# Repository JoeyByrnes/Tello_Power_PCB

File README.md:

# Tello Power PCB
Hardware Design Files for Tello Power Regulation/Distribution PCB

## Main Power PCB
<hr>
<br>

<br>

## XT30 Expansion PCB
<hr>
<br>

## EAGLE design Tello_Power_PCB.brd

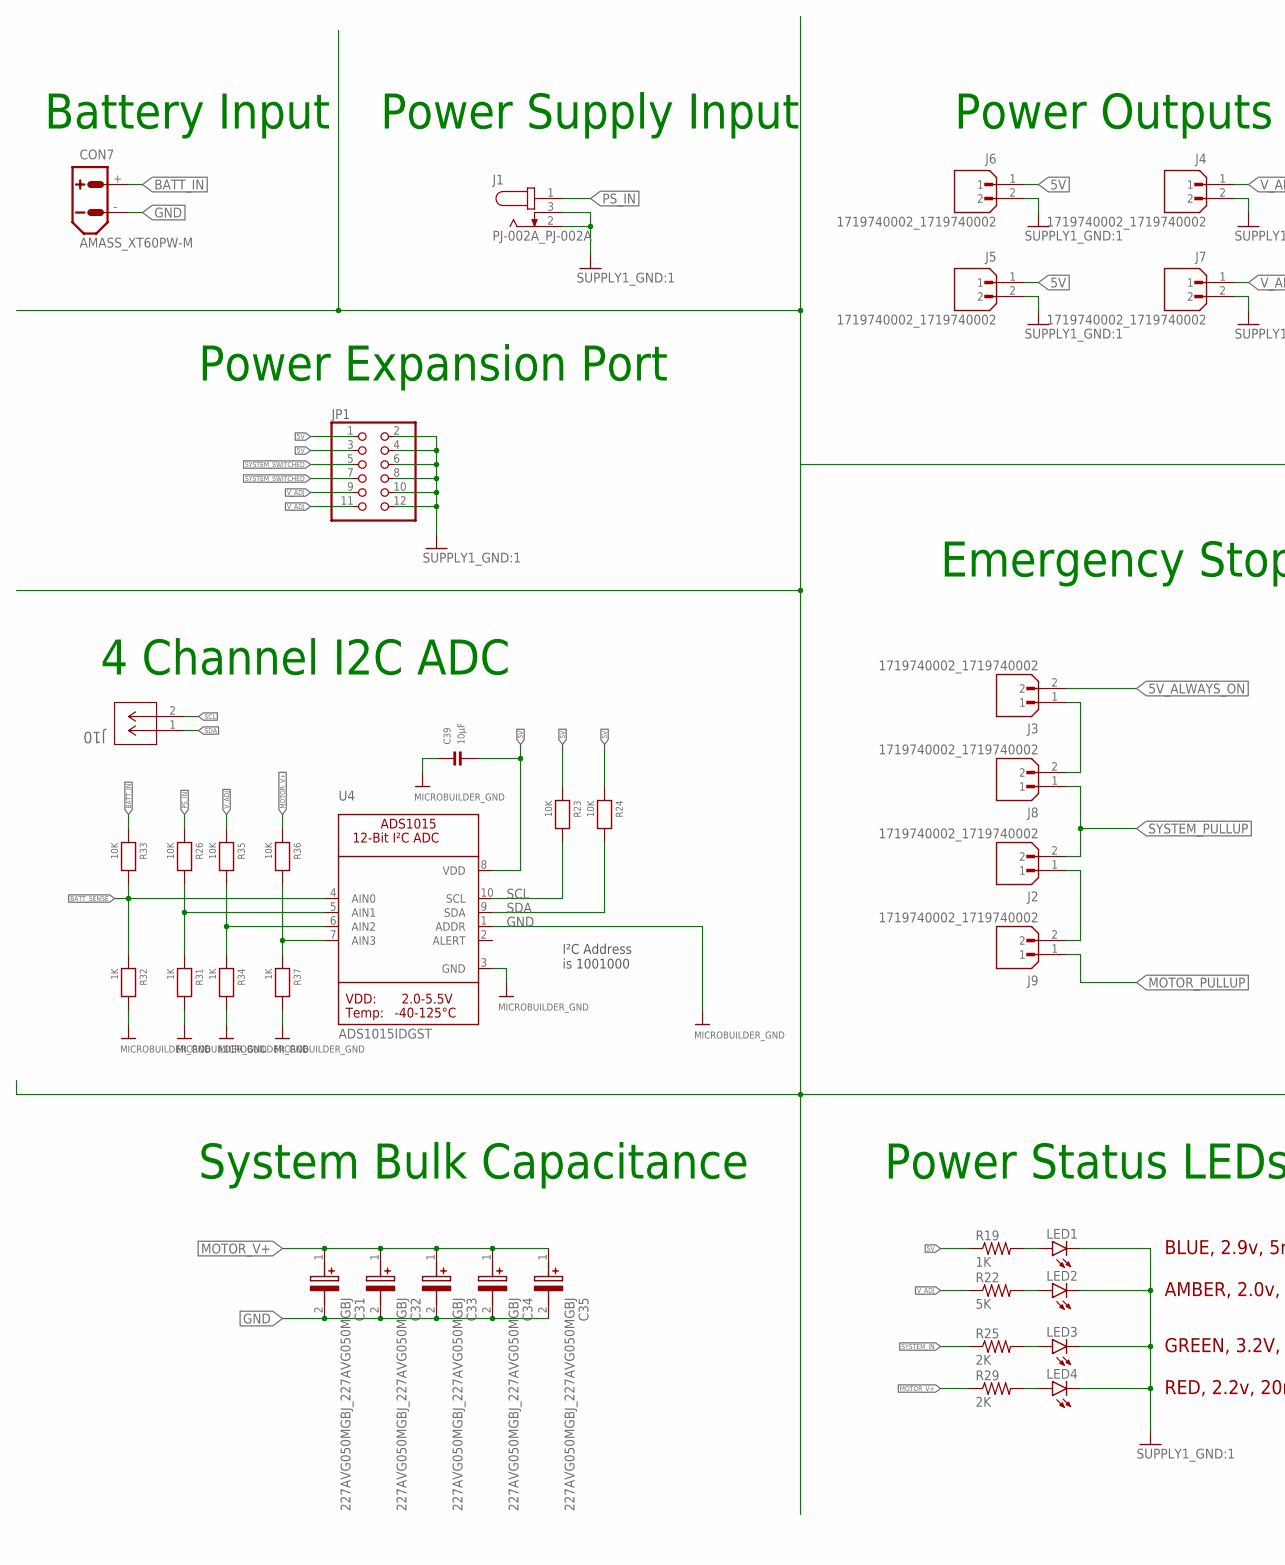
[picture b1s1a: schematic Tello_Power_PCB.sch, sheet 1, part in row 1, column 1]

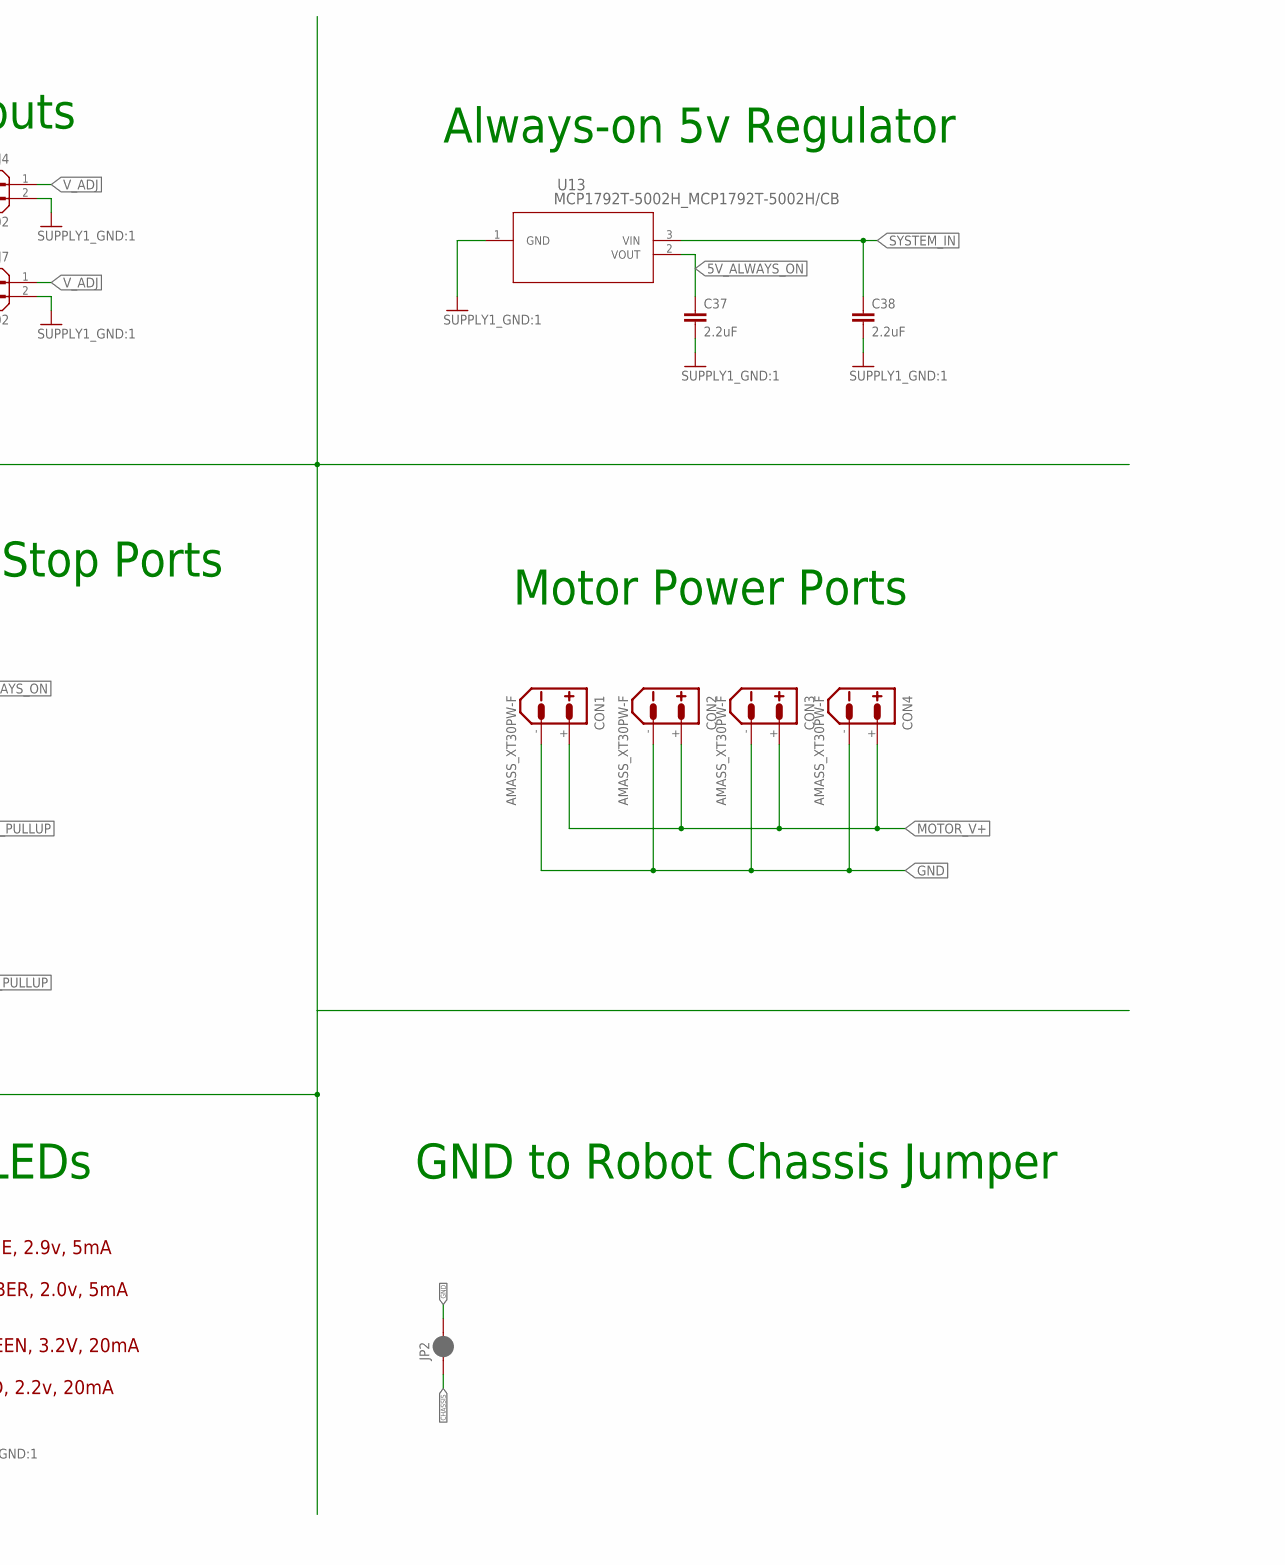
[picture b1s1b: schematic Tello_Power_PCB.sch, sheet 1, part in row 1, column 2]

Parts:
C31, C32, C33, C34, C35: 227AVG050MGBJ_227AVG050MGBJ; 227AVG050MGBJ_CAPPRD500W60D1025H1350
C37: 2.2uF; RCL_C0603
C38: 2.2uF; RCL_C1206
C39: 10µF; MICROBUILDER_0603:1
CON1, CON2, CON3, CON4: AMASS_XT30PW-F
CON7: AMASS_XT60PW-M
J1: PJ-002A_PJ-002A; PJ-002A_CUI_PJ-002A
J2, J3, J4, J5, J6, J7, J8, J9: 1719740002_1719740002; 1719740002_MOLEX_1719740002
J10: SM02B-GHS-TB_SM02BGHSTBLFSN; SM02B-GHS-TB_CONN_SM02BGHSTB_JST
JP1: PINHEAD_PINHD-2X6; PINHEAD_2X06
JP2: SPARKFUN-JUMPERS_JUMPER-SMT_2_NC_PASTE_NO-SILK; SPARKFUN-JUMPERS_SMT-JUMPER_2_NC_PASTE_NO-SILK
LED1, LED2, LED3, LED4: LED_LEDCHIP-LED0603; LED_CHIP-LED0603
R19: 1K; RCL_R0603
R22: 5K; RCL_R0603
R23, R24, R26, R33, R35, R36: 10K; MICROBUILDER_0603:1
R25, R29: 2K; RCL_R0603
R31, R32, R34, R37: 1K; MICROBUILDER_0603:1
U4: ADS1015IDGST; MICROBUILDER_MSOP10
U13: MCP1792T-5002H_MCP1792T-5002H/CB; MCP1792T-5002H_SOT-23A_CB_MCH

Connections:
5V: C39.2, J5.1, J6.1, JP1.1, JP1.3, R19.1, R23.1, R24.1, U4.8 (VDD); also elsewhere on the board
5V_ALWAYS_ON: C37.1, J3.2, U13.2 (VOUT); also elsewhere on the board
BATT_IN: CON7.+, R33.1; also elsewhere on the board
BATT_SENSE: R32.1, R33.2, U4.4 (AIN0)
CHASSIS: JP2.1
GND: C31.2 (-), C32.2 (-), C33.2 (-), C34.2 (-), C35.2 (-), C37.2, C38.2, C39.1, CON1.-, CON2.-, CON3.-, CON4.-, CON7.-, J1.2, J1.3, J4.2, J5.2, J6.2, J7.2, JP1.2, JP1.4, JP1.6, JP1.8, JP1.10, JP1.12, JP2.2, LED1.C, LED2.C, LED3.C, LED4.C, R31.2, R32.2, R34.2, R37.2, U4.1 (ADDR), U4.3 (GND), U13.1 (GND); also elsewhere on the board
MOTOR_PULLUP: J9.1; also elsewhere on the board
MOTOR_V+: C31.1 (+), C32.1 (+), C33.1 (+), C34.1 (+), C35.1 (+), CON1.+, CON2.+, CON3.+, CON4.+, R29.1, R36.1; also elsewhere on the board
unnamed: LED4.A, R29.2
unnamed: R26.2, R31.1, U4.5 (AIN1)
unnamed: J2.1, J9.2
unnamed: R34.1, R35.2, U4.6 (AIN2)
unnamed: J3.1, J8.2
unnamed: R36.2, R37.1, U4.7 (AIN3)
unnamed: LED3.A, R25.2
unnamed: LED2.A, R22.2
unnamed: LED1.A, R19.2
PS_IN: J1.1, R26.1; also elsewhere on the board
SCL: J10.2, R23.2, U4.10 (SCL)
SDA: J10.1, R24.2, U4.9 (SDA)
SYSTEM_IN: C38.1, R25.1, U13.3 (VIN); also elsewhere on the board
SYSTEM_PULLUP: J2.2, J8.1; also elsewhere on the board
SYSTEM_SWITCHED: JP1.5, JP1.7; also elsewhere on the board
V_ADJ: J4.1, J7.1, JP1.9, JP1.11, R22.1, R35.1; also elsewhere on the board

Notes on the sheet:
Power Supply Input
Battery Input
RED, 2.2v, 20mA
GREEN, 3.2V, 20mA
AMBER, 2.0v, 5mA
BLUE, 2.9v, 5mA
Power Outputs
Power Expansion Port
System Bulk Capacitance
Power Status LEDs
Emergency Stop Ports
Motor Power Ports
Always-on 5v Regulator
GND to Robot Chassis Jumper
I²C Address is 1001000
4 Channel I2C ADC

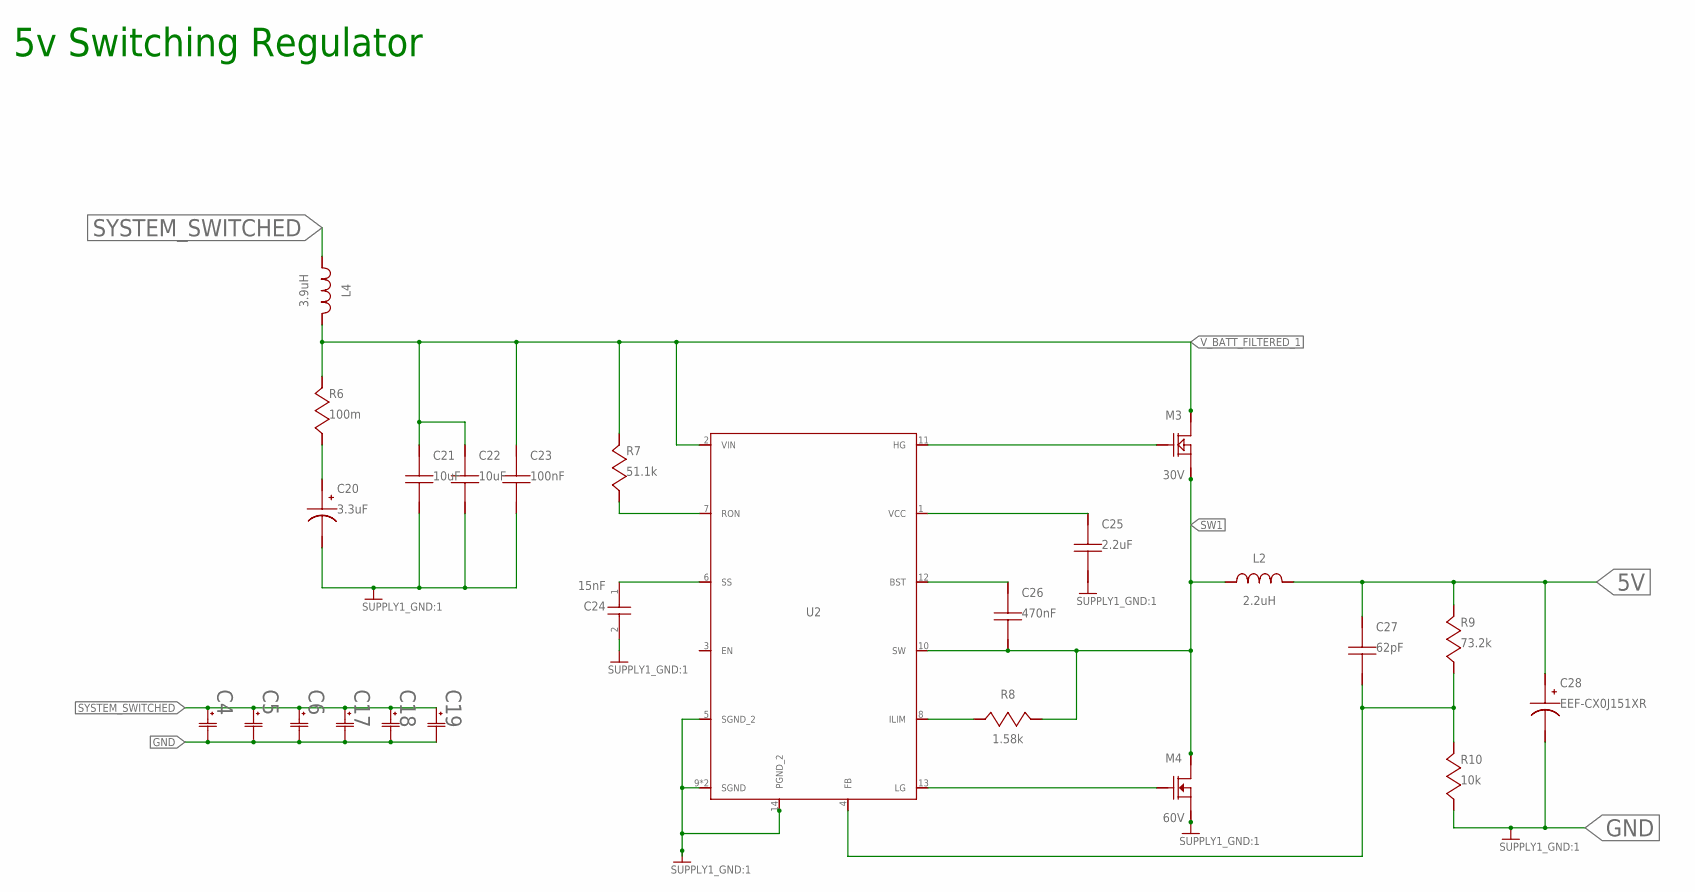
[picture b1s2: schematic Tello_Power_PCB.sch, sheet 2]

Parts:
C4, C5, C6, C17, C18, C19: PCR1H820MCL1GS_PCR1H820MCL1GS; PCR1H820MCL1GS_CAP_PC_10X8_NCH
C20: 3.3uF; 5V-LM3150MH_6032-28
C21, C22: 10uF; 5V-LM3150MH_0805
C23: 100nF; 5V-LM3150MH_0603
C24: 15nF; CGA4F2C0G1H153J085AA_CAPC2012X100N
C25: 2.2uF; 5V-LM3150MH_0805
C26: 470nF; 5V-LM3150MH_1206
C27: 62pF; 5V-LM3150MH_0805
C28: EEF-CX0J151XR; 5V-LM3150MH_C2917
L2: 2.2uH; 5V-LM3150MH_XAL5030
L4: 3.9uH; 5V-LM3150MH_IND_NPI43C
M3: 30V; 5V-LM3150MH_TRANS_NEXFET_Q5A
M4: 60V; 5V-LM3150MH_TRANS_NEXFET_Q5A
R6: 100m; 5V-LM3150MH_0603
R7: 51.1k; 5V-LM3150MH_0805
R8: 1.58k; 5V-LM3150MH_0805
R9: 73.2k; 5V-LM3150MH_0805
R10: 10k; 5V-LM3150MH_0805
U2: 5V-LM3150MH_LM3150MH/NOPB; 5V-LM3150MH_MXA14A

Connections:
5V: C27.1, C28.P$1 (+), L2.2, R9.1; also elsewhere on the board
GND: C4.2, C5.2, C6.2, C17.2, C18.2, C19.2, C20.2 (-), C21.2, C22.2, C23.2, C24.2, C25.2, C28.P$2 (-), M4.1 (SOURCE), M4.2 (SOURCE), M4.3 (SOURCE), R10.2, U2.5 (SGND_2), U2.9 (SGND), U2.14 (PGND_2), U2.15 (SGND); also elsewhere on the board
unnamed: R7.2, U2.7 (RON)
unnamed: C24.1, U2.6 (SS)
unnamed: C20.1 (+), R6.2
unnamed: R8.2, U2.8 (ILIM)
unnamed: C26.1, U2.12 (BST)
unnamed: C25.1, U2.1 (VCC)
unnamed: M3.4 (GATE), U2.11 (HG)
unnamed: M4.4 (GATE), U2.13 (LG)
unnamed: C27.2, R9.2, R10.1, U2.4 (FB)
SW1: C26.2, L2.1, M3.1 (SOURCE), M3.2 (SOURCE), M3.3 (SOURCE), M4.5 (DRAIN), M4.6 (DRAIN), M4.7 (DRAIN), M4.8 (DRAIN), M4.9 (DRAIN), R8.1, U2.10 (SW)
SYSTEM_SWITCHED: C4.1, C5.1, C6.1, C17.1, C18.1, C19.1, L4.1; also elsewhere on the board
V_BATT_FILTERED_1: C21.1, C22.1, C23.1, L4.2, M3.5 (DRAIN), M3.6 (DRAIN), M3.7 (DRAIN), M3.8 (DRAIN), M3.9 (DRAIN), R6.1, R7.1, U2.2 (VIN)

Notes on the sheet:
5v Switching Regulator

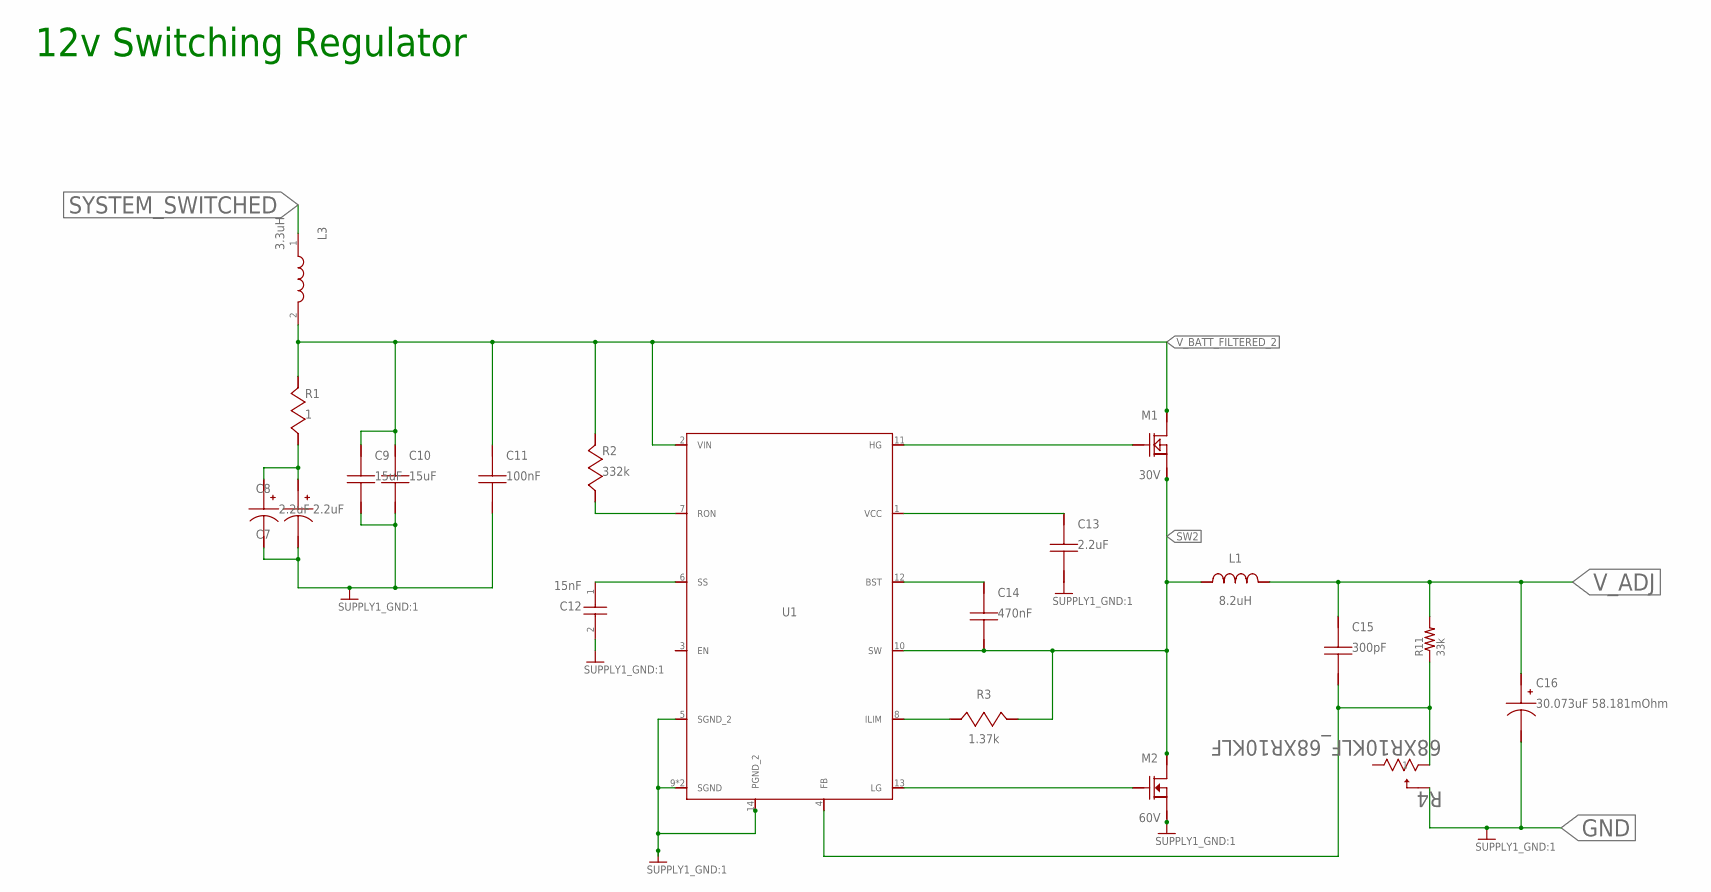
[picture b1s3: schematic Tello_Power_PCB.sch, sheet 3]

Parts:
C7, C8: 2.2uF; 12V--LM3150_3528-21
C9, C10: 15uF; 12V--LM3150_0805:1
C11: 100nF; 12V--LM3150_0402
C12: 15nF; CGA4F2C0G1H153J085AA_CAPC2012X100N
C13: 2.2uF; 12V--LM3150_0805:1
C14: 470nF; 12V--LM3150_1206:1
C15: 300pF; 12V--LM3150_0805:1
C16: 30.073uF 58.181mOhm; 12V--LM3150_PCV1E330MCL1GS
L1: 8.2uH; 12V--LM3150_WE-LHMI_8040
L3: 3.3uH; XAL4030-332MEB_XAL4030-332MEB
M1: 30V; 12V--LM3150_TRANS_NEXFET_Q5A:1
M2: 60V; 12V--LM3150_TRANS_NEXFET_Q5A:1
R1: 1; 12V--LM3150_0402
R2: 332k; 12V--LM3150_0805:1
R3: 1.37k; 12V--LM3150_0805:1
R4: 68XR10KLF_68XR10KLF; 68XR10KLF_RES3_68X_TTE
R11: 33k; RCL_R0805
U1: 5V-LM3150MH_LM3150MH/NOPB; 5V-LM3150MH_MXA14A

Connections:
GND: C7.2 (-), C8.2 (-), C9.2, C10.2, C11.2, C12.2, C13.2, C16.P$3 (-), M2.1 (SOURCE), M2.2 (SOURCE), M2.3 (SOURCE), R4.2, U1.5 (SGND_2), U1.9 (SGND), U1.14 (PGND_2), U1.15 (SGND); also elsewhere on the board
unnamed: C7.1 (+), C8.1 (+), R1.2
unnamed: R2.2, U1.7 (RON)
unnamed: C12.1, U1.6 (SS)
unnamed: R3.2, U1.8 (ILIM)
unnamed: C14.1, U1.12 (BST)
unnamed: C13.1, U1.1 (VCC)
unnamed: M1.4 (GATE), U1.11 (HG)
unnamed: M2.4 (GATE), U1.13 (LG)
unnamed: C15.2, R4.3 (1), R11.1, U1.4 (FB)
SW2: C14.2, L1.1, M1.1 (SOURCE), M1.2 (SOURCE), M1.3 (SOURCE), M2.5 (DRAIN), M2.6 (DRAIN), M2.7 (DRAIN), M2.8 (DRAIN), M2.9 (DRAIN), R3.1, U1.10 (SW)
SYSTEM_SWITCHED: L3.1; also elsewhere on the board
V_ADJ: C15.1, C16.P$1 (+), L1.2, R11.2; also elsewhere on the board
V_BATT_FILTERED_2: C9.1, C10.1, C11.1, L3.2, M1.5 (DRAIN), M1.6 (DRAIN), M1.7 (DRAIN), M1.8 (DRAIN), M1.9 (DRAIN), R1.1, R2.1, U1.2 (VIN)

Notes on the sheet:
12v Switching Regulator

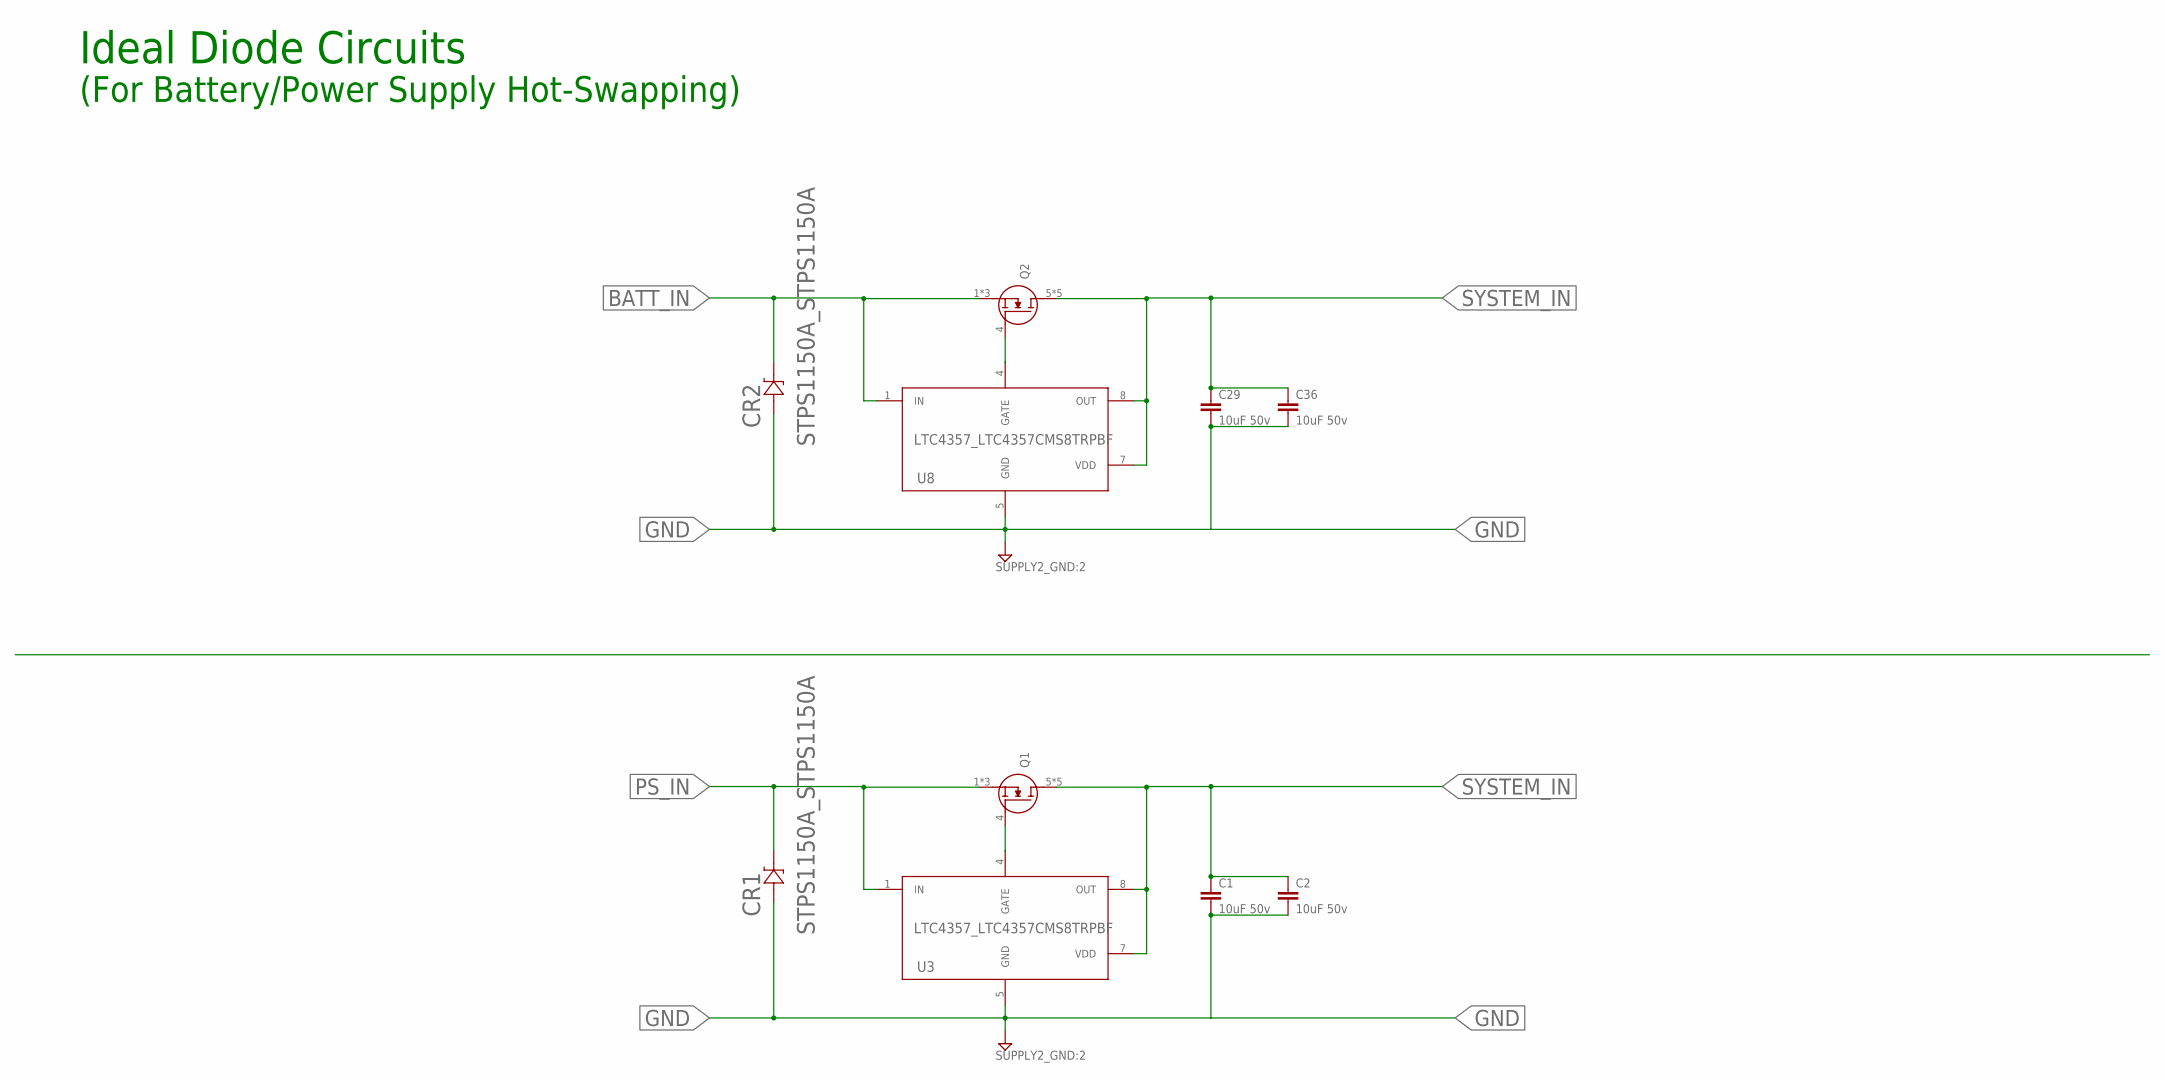
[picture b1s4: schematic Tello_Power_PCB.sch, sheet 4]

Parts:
C1, C2, C29, C36: 10uF 50v; RCL_C1206
CR1, CR2: STPS1150A_STPS1150A; STPS1150A_SMA_STM
Q1, Q2: BSC027N06LS5ATMA1_BSC027N06LS5ATMA1
U3, U8: LTC4357_LTC4357CMS8TRPBF; LTC4357_MSOP-8_MS_LIT

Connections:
BATT_IN: CR2.1, Q2.1 (S), Q2.2 (S), Q2.3 (S), U8.1 (IN); also elsewhere on the board
GND: C1.2, C2.2, C29.2, C36.2, CR1.2, CR2.2, U3.5 (GND), U8.5 (GND); also elsewhere on the board
unnamed: Q1.4 (G), U3.4 (GATE)
unnamed: Q2.4 (G), U8.4 (GATE)
PS_IN: CR1.1, Q1.1 (S), Q1.2 (S), Q1.3 (S), U3.1 (IN); also elsewhere on the board
SYSTEM_IN: C1.1, C2.1, C29.1, C36.1, Q1.5 (D), Q1.6 (D), Q1.7 (D), Q1.8 (D), Q1.9 (D), Q2.5 (D), Q2.6 (D), Q2.7 (D), Q2.8 (D), Q2.9 (D), U3.7 (VDD), U3.8 (OUT), U8.7 (VDD), U8.8 (OUT); also elsewhere on the board

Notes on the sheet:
Ideal Diode Circuits
(For Battery/Power Supply Hot-Swapping)

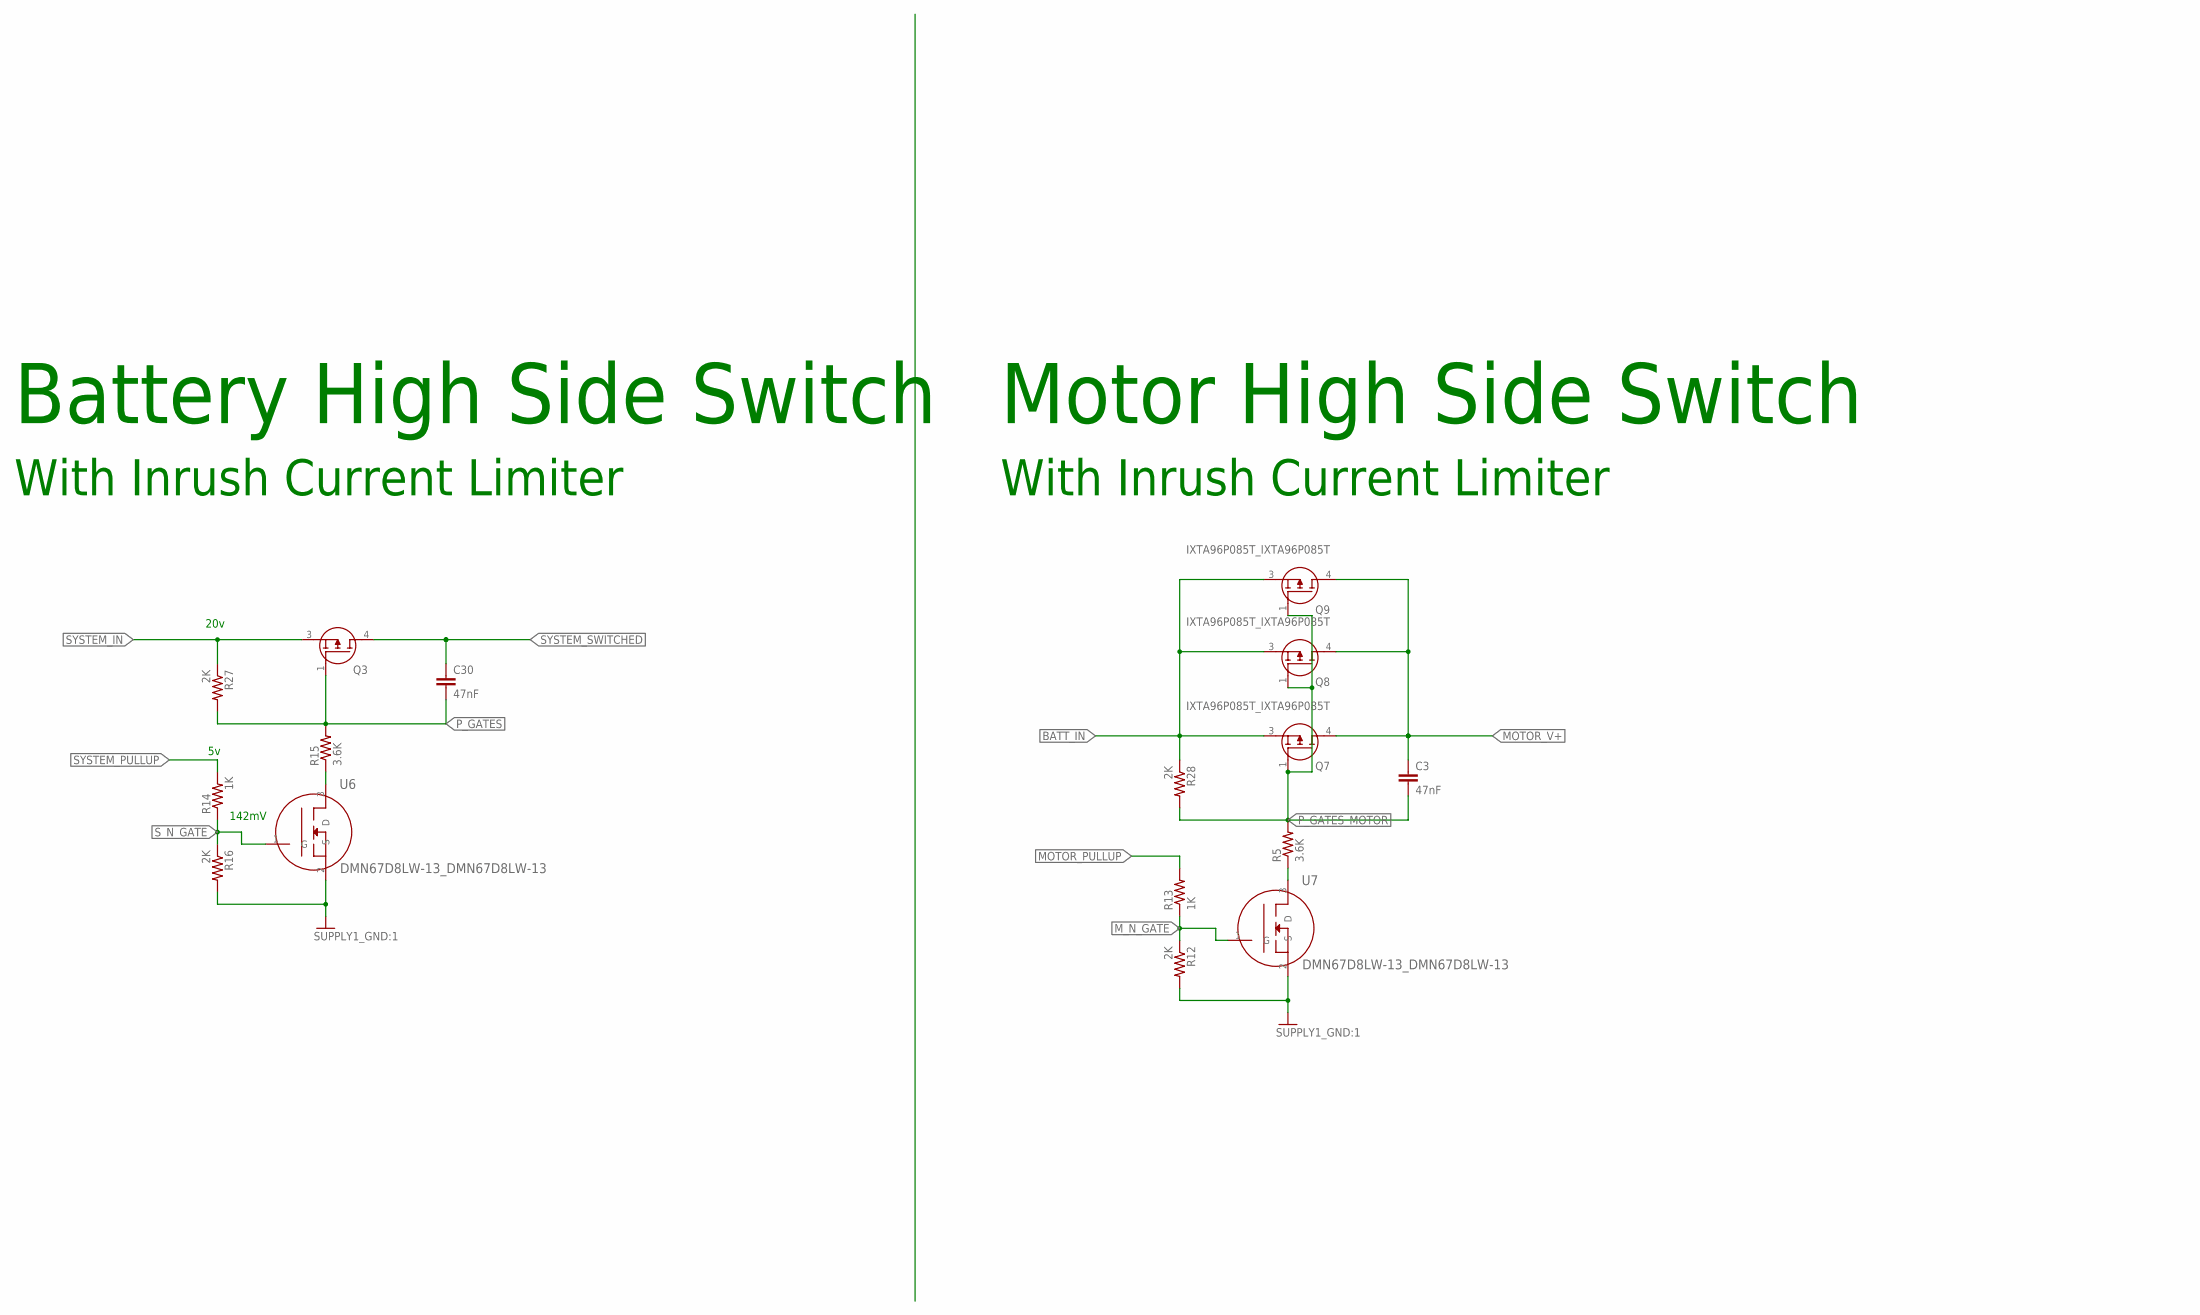
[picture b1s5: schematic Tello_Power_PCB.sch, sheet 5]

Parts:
C3, C30: 47nF; RCL_C0603
Q3, Q7, Q8, Q9: IXTA96P085T_IXTA96P085T
R5, R15: 3.6K; RCL_R0603
R12, R16, R27, R28: 2K; RCL_R0603
R13, R14: 1K; RCL_R0603
U6, U7: DMN67D8LW-13_DMN67D8LW-13; DMN67D8LW-13_DMN67D8LW-13_DIO

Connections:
BATT_IN: Q7.3 (S), Q8.3 (S), Q9.3 (S), R28.1; also elsewhere on the board
GND: R12.2, R16.2, U6.2 (S), U7.2 (S); also elsewhere on the board
MOTOR_PULLUP: R13.2; also elsewhere on the board
MOTOR_V+: C3.1, Q7.4 (D), Q8.4 (D), Q9.4 (D); also elsewhere on the board
M_N_GATE: R12.1, R13.1, U7.1 (G); also elsewhere on the board
unnamed: R5.1, U7.3 (D)
unnamed: R15.1, U6.3 (D)
P_GATES: C30.2, Q3.1 (G), R15.2, R27.2
P_GATES_MOTOR: C3.2, Q7.1 (G), Q8.1 (G), Q9.1 (G), R5.2, R28.2
SYSTEM_IN: Q3.3 (S), R27.1; also elsewhere on the board
SYSTEM_PULLUP: R14.2; also elsewhere on the board
SYSTEM_SWITCHED: C30.1, Q3.4 (D); also elsewhere on the board
S_N_GATE: R14.1, R16.1, U6.1 (G); also elsewhere on the board

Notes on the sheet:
Battery High Side Switch
With Inrush Current Limiter
Motor High Side Switch
20v
142mV

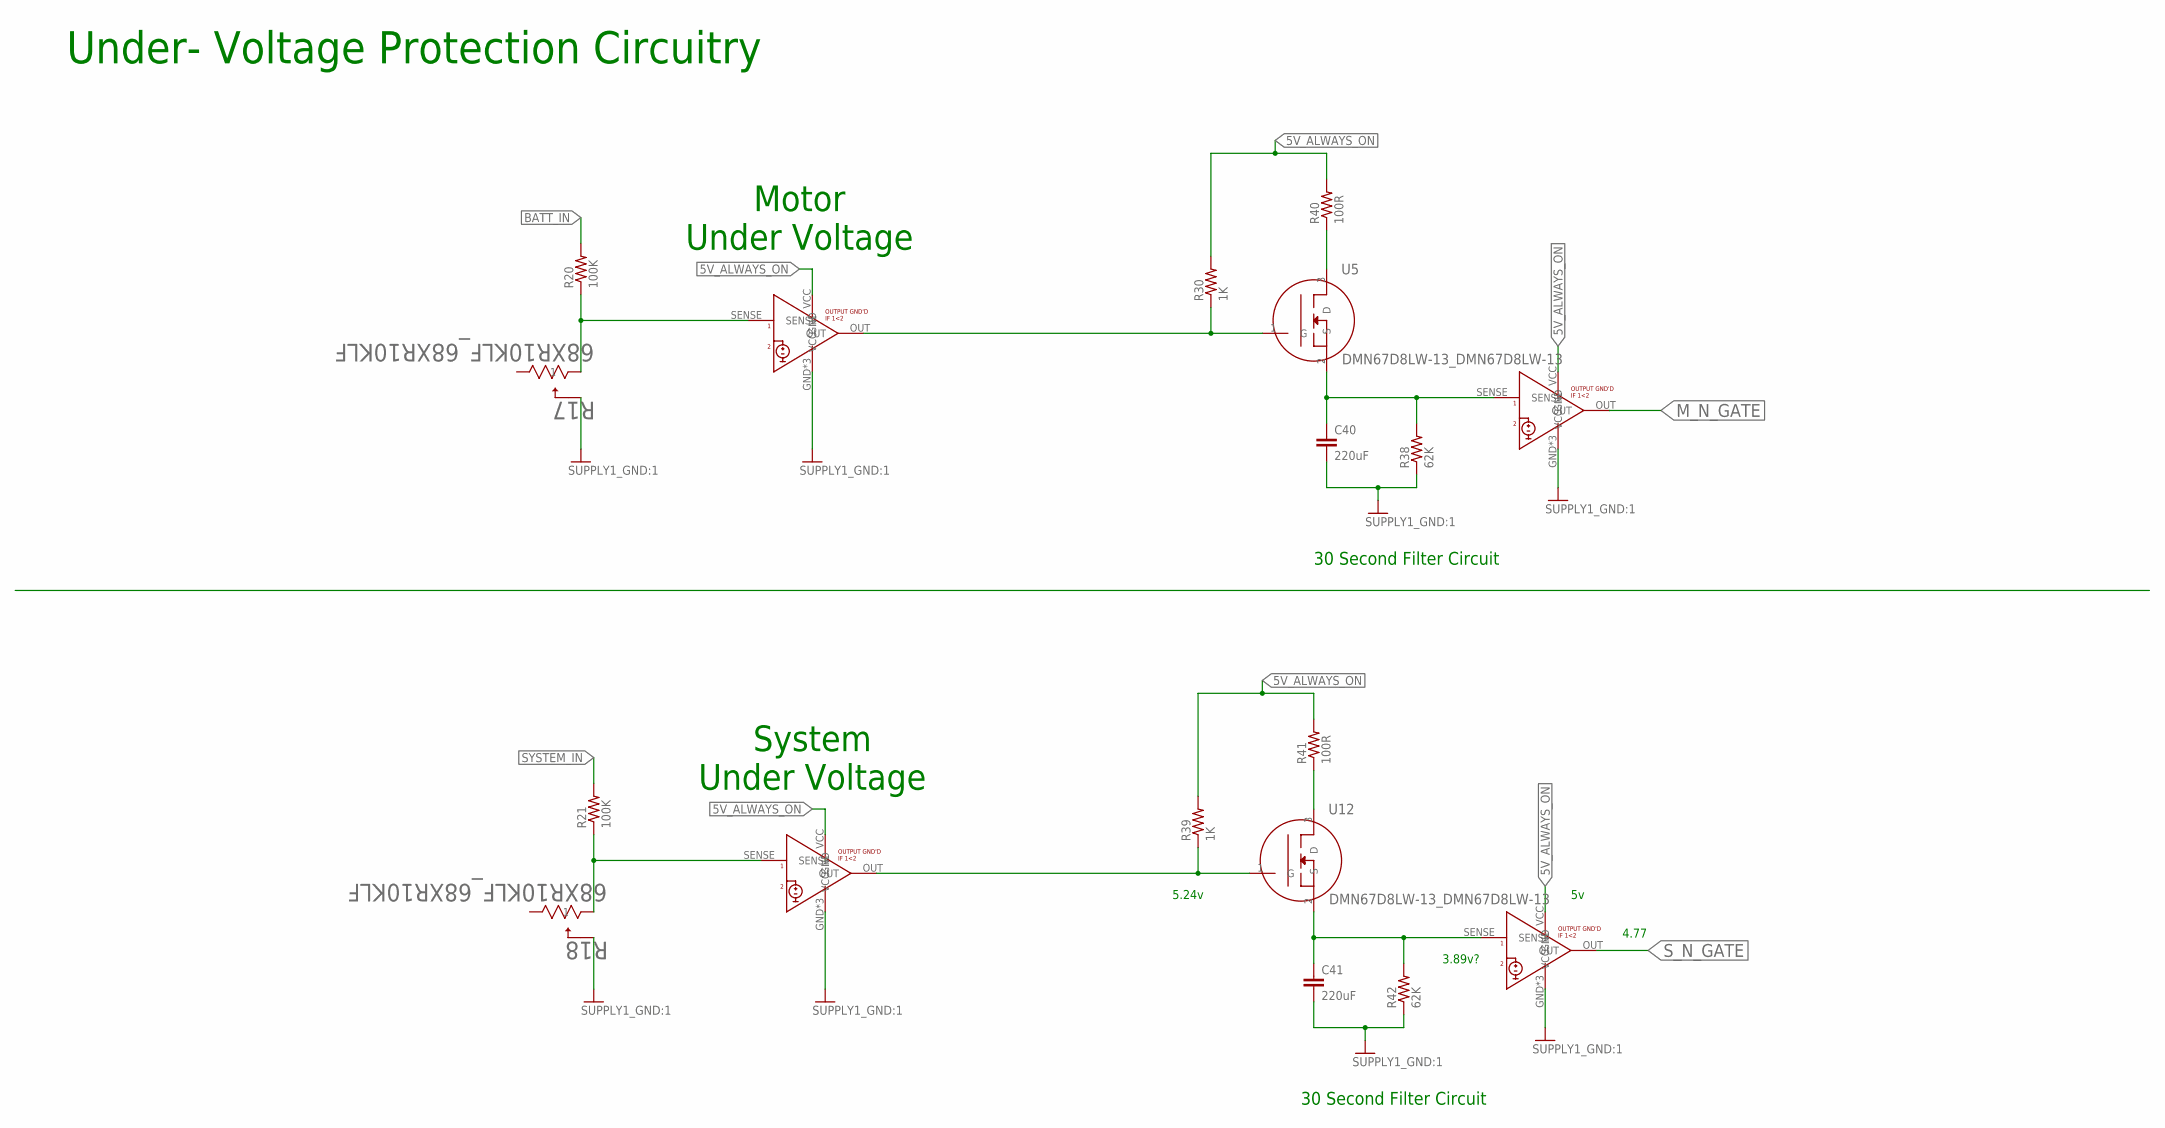
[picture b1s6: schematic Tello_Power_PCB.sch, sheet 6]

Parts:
C40, C41: 220uF; RCL_C1210
R17, R18: 68XR10KLF_68XR10KLF; 68XR10KLF_RES3_68X_TTE
R20, R21: 100K; RCL_R0603
R30, R39: 1K; RCL_R0603
R38, R42: 62K; RCL_R0603
R40, R41: 100R; RCL_R0603
U5, U12: DMN67D8LW-13_DMN67D8LW-13; DMN67D8LW-13_DMN67D8LW-13_DIO
U9, U10, U11, U14: TLV6713DDC_TLV6713DDCTDDC0006A_M; TLV6713DDC_DDC0006A_M

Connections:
5V_ALWAYS_ON: R30.2, R39.2, R40.2, R41.2, U9.VCC, U10.VCC, U11.VCC, U14.VCC; also elsewhere on the board
BATT_IN: R20.2; also elsewhere on the board
GND: C40.2, C41.2, R17.2, R18.2, R38.1, R42.1, U9.GND, U9.GND@1 (GND), U9.GND@2 (GND), U10.GND, U10.GND@1 (GND), U10.GND@2 (GND), U11.GND, U11.GND@1 (GND), U11.GND@2 (GND), U14.GND, U14.GND@1 (GND), U14.GND@2 (GND); also elsewhere on the board
M_N_GATE: U11.OUT; also elsewhere on the board
unnamed: R30.1, U5.1 (G), U10.OUT
unnamed: R18.3 (1), R21.1, U9.SENSE
unnamed: R17.3 (1), R20.1, U10.SENSE
unnamed: C40.1, R38.2, U5.2 (S), U11.SENSE
unnamed: R40.1, U5.3 (D)
unnamed: R39.1, U9.OUT, U12.1 (G)
unnamed: R41.1, U12.3 (D)
unnamed: C41.1, R42.2, U12.2 (S), U14.SENSE
SYSTEM_IN: R21.2; also elsewhere on the board
S_N_GATE: U14.OUT; also elsewhere on the board

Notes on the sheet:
System Under Voltage
Motor Under Voltage
30 Second Filter Circuit
Under- Voltage Protection Circuitry
3.89v?
5.24v
4.77

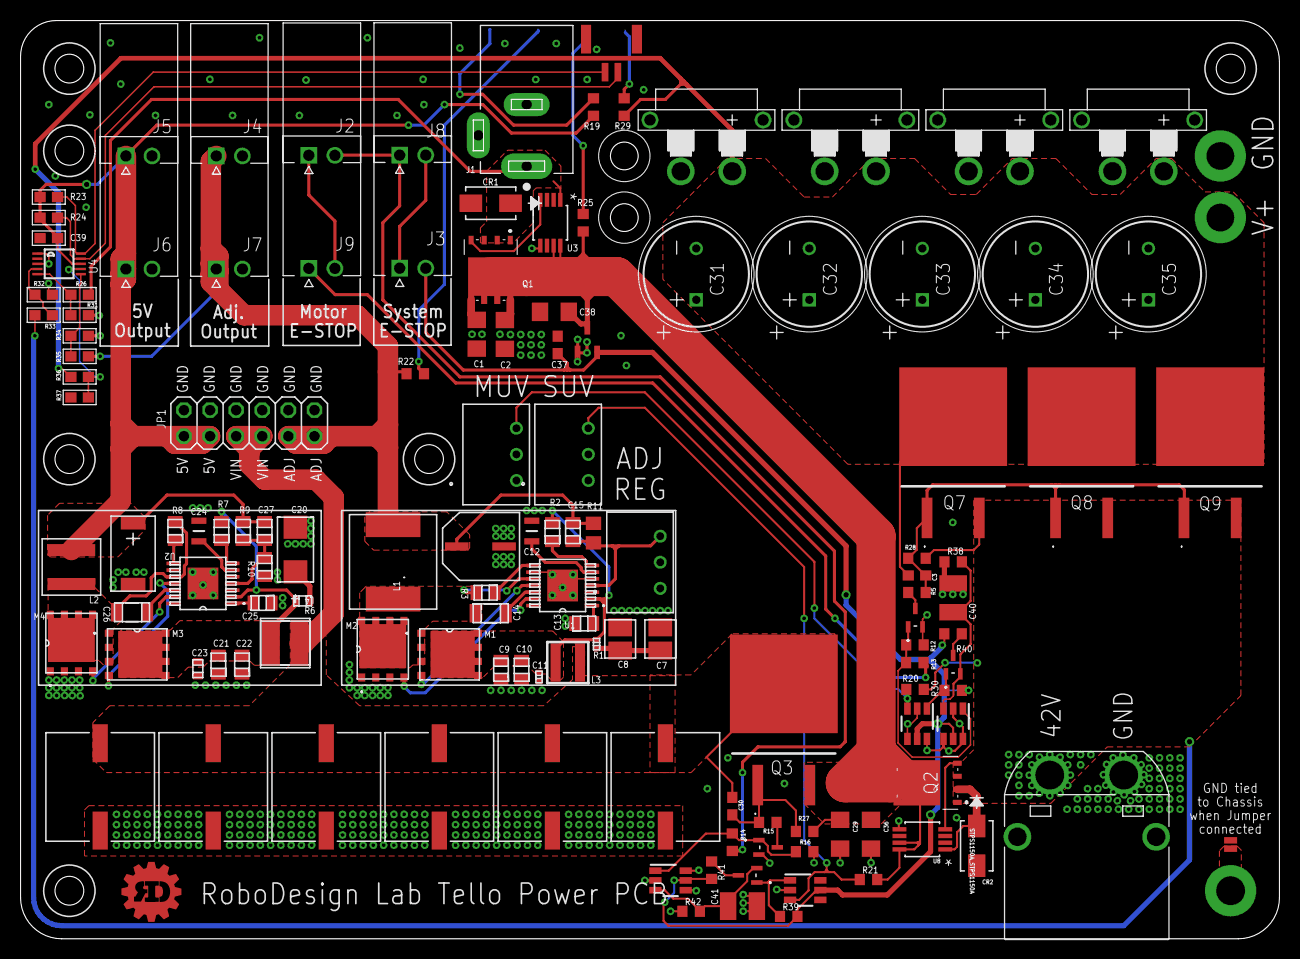
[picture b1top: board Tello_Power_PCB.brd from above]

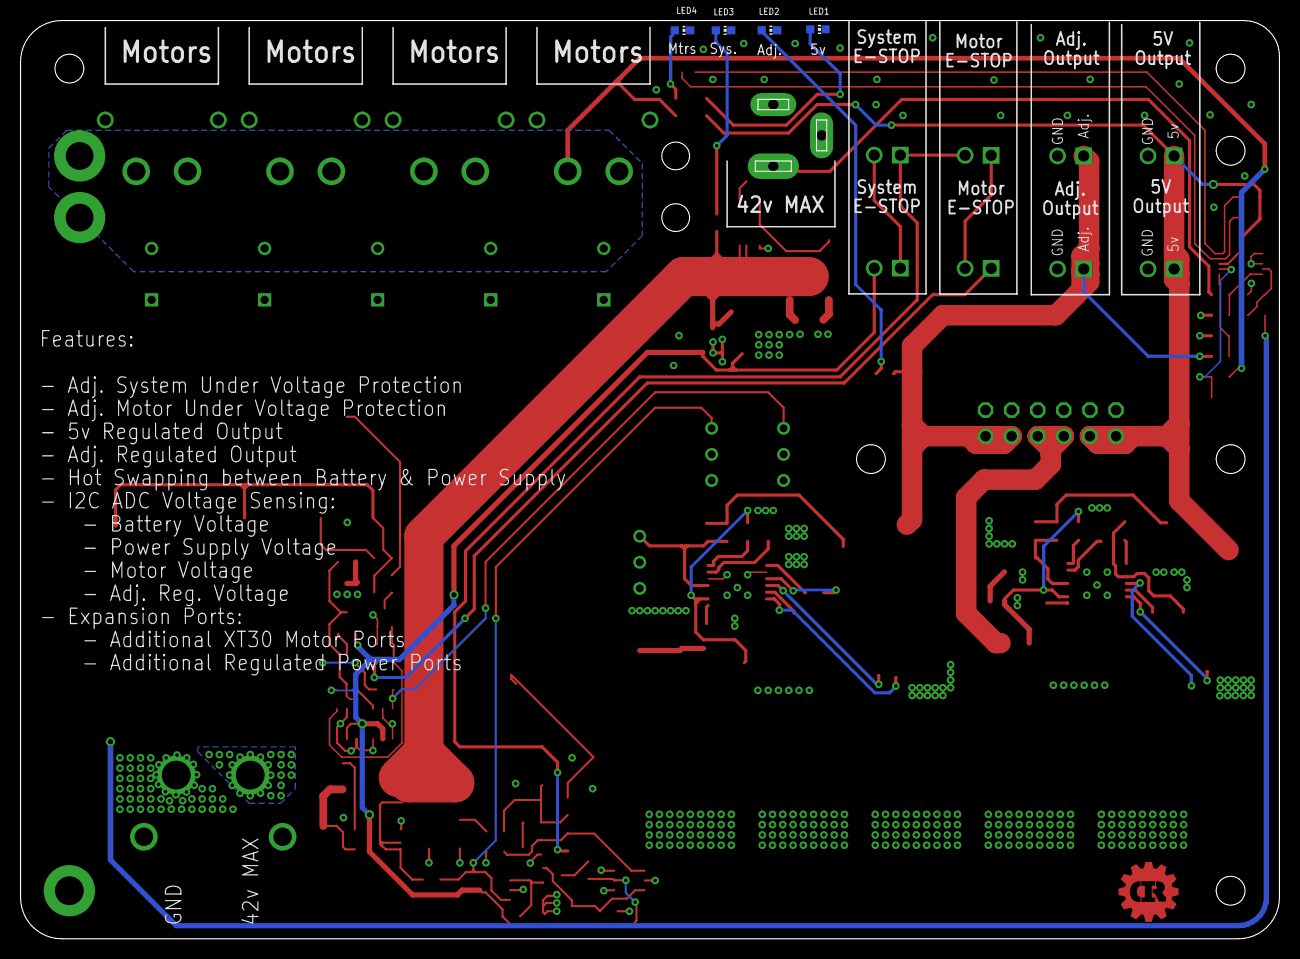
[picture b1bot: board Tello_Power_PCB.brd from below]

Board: 4 copper layers, 122.5 x 89.3 mm, 134 parts (4 on the bottom side), 61 nets.

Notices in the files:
parts and their libraries:
COPYRIGHT: Copyright (C) 2022 Ultra Librarian. All rights reserved.
